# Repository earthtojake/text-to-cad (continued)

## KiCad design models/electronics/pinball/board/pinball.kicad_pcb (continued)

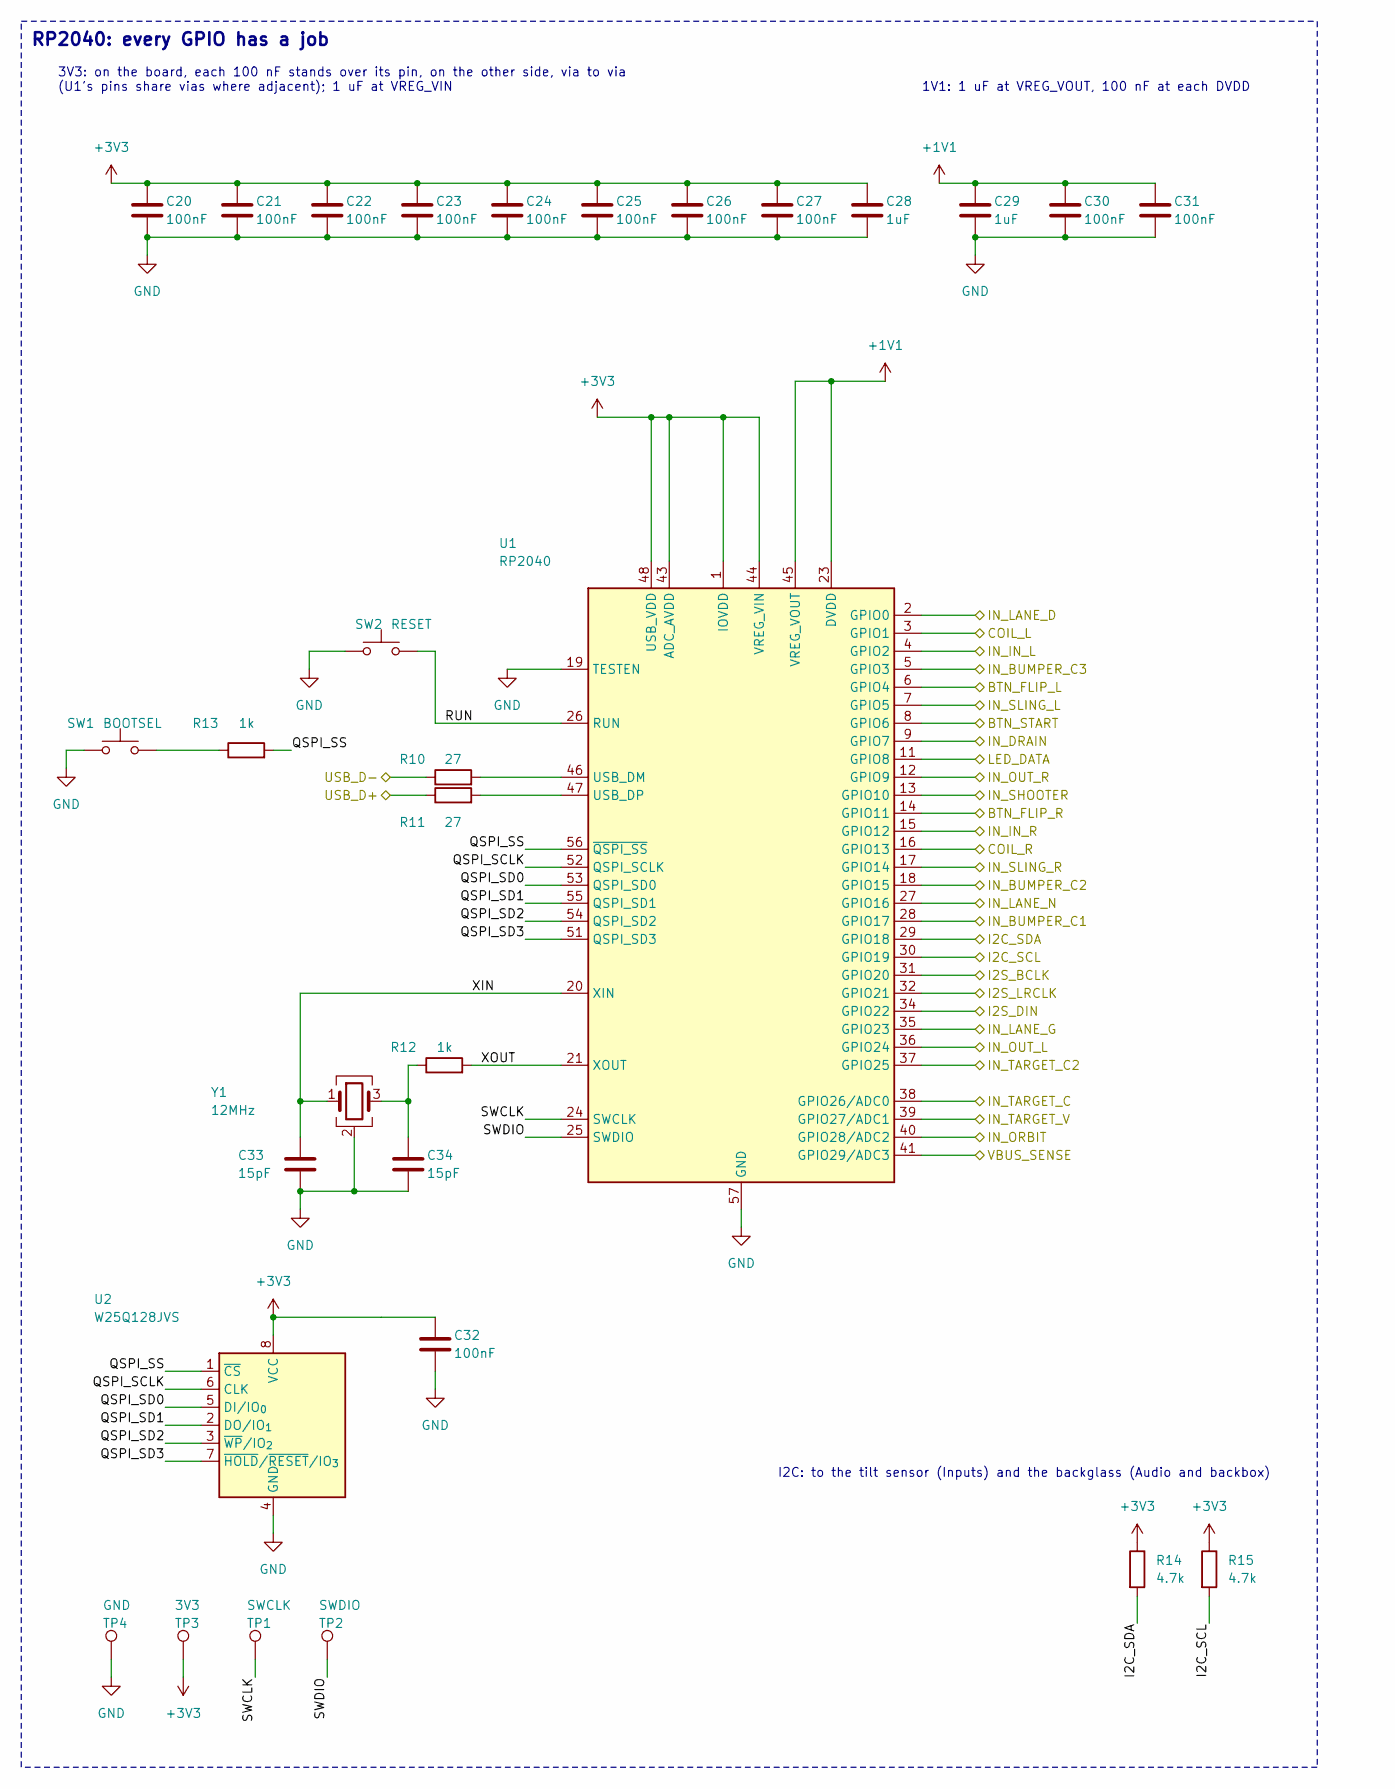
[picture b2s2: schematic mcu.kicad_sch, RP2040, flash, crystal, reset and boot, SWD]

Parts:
C20, C21, C22, C23, C24, C25, C26, C27, C30, C31, C32: 100nF; C_0402_1005Metric; MPN CL05B104KO5NNNC; LCSC C1525
C28: 1uF; C_0603_1608Metric; MPN CL10A105KB8NNNC; LCSC C15849
C29: 1uF; C_0402_1005Metric; MPN CL05A105KA5NQNC; LCSC C52923
C33, C34: 15pF; C_0402_1005Metric; MPN 0402CG150J500NT; LCSC C1548
R10, R11: 27; R_0402_1005Metric; MPN 0402WGF270JTCE; LCSC C25092
R12, R13: 1k; R_0402_1005Metric; MPN 0402WGF1001TCE; LCSC C11702
R14, R15: 4.7k; R_0402_1005Metric; MPN 0402WGF4701TCE; LCSC C25900
SW1: BOOTSEL; SW_SPST_TL3342; MPN TL3342F160QG
SW2: RESET; SW_SPST_TL3342; MPN TL3342F160QG
TP1: SWCLK; TestPoint_Pad_D1.5mm
TP2: SWDIO; TestPoint_Pad_D1.5mm
TP3: 3V3; TestPoint_Pad_D1.5mm
TP4: GND; TestPoint_Pad_D1.5mm
U1: RP2040; QFN-56-1EP_7x7mm_P0.4mm_EP3.2x3.2mm; MPN RP2040; LCSC C2040
U2: W25Q128JVS; SOIC-8_5.3x5.3mm_P1.27mm; MPN W25Q128JVSIQ; LCSC C97521
Y1: 12MHz; Crystal_SMD_3225-4Pin_3.2x2.5mm; MPN X322512MSB4SI; LCSC C9002

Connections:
+1V1: C29.1, C30.1, C31.1, U1.23 (DVDD), U1.45 (VREG_VOUT), U1.50 (DVDD)
+3V3: C20.1, C21.1, C22.1, C23.1, C24.1, C25.1, C26.1, C27.1, C28.1, C32.1, R14.1, R15.1, TP3.1 (1_1), U1.1 (IOVDD), U1.10 (IOVDD), U1.22 (IOVDD), U1.33 (IOVDD), U1.42 (IOVDD), U1.43 (ADC_AVDD), U1.44 (VREG_VIN), U1.48 (USB_VDD), U1.49 (IOVDD), U2.8 (VCC); also elsewhere on the board
/Audio and backbox/I2S_BCLK: U1.31 (GPIO20); also elsewhere on the board
/Audio and backbox/I2S_DIN: U1.34 (GPIO22); also elsewhere on the board
/Audio and backbox/I2S_LRCLK: U1.32 (GPIO21); also elsewhere on the board
/Flippers/COIL_L: U1.3 (GPIO1); also elsewhere on the board
/Flippers/COIL_R: U1.16 (GPIO13); also elsewhere on the board
/I2C_SCL: R15.2, U1.30 (GPIO19); also elsewhere on the board
/I2C_SDA: R14.2, U1.29 (GPIO18); also elsewhere on the board
/Inputs/BTN_FLIP_L: U1.6 (GPIO4); also elsewhere on the board
/Inputs/BTN_FLIP_R: U1.14 (GPIO11); also elsewhere on the board
/Inputs/BTN_START: U1.8 (GPIO6); also elsewhere on the board
/Inputs/IN_BUMPER_C1: U1.28 (GPIO17); also elsewhere on the board
/Inputs/IN_BUMPER_C2: U1.18 (GPIO15); also elsewhere on the board
/Inputs/IN_BUMPER_C3: U1.5 (GPIO3); also elsewhere on the board
/Inputs/IN_DRAIN: U1.9 (GPIO7); also elsewhere on the board
/Inputs/IN_IN_L: U1.4 (GPIO2); also elsewhere on the board
/Inputs/IN_IN_R: U1.15 (GPIO12); also elsewhere on the board
/Inputs/IN_LANE_D: U1.2 (GPIO0); also elsewhere on the board
/Inputs/IN_LANE_G: U1.35 (GPIO23); also elsewhere on the board
/Inputs/IN_LANE_N: U1.27 (GPIO16); also elsewhere on the board
/Inputs/IN_ORBIT: U1.40 (GPIO28/ADC2); also elsewhere on the board
/Inputs/IN_OUT_L: U1.36 (GPIO24); also elsewhere on the board
/Inputs/IN_OUT_R: U1.12 (GPIO9); also elsewhere on the board
/Inputs/IN_SHOOTER: U1.13 (GPIO10); also elsewhere on the board
/Inputs/IN_SLING_L: U1.7 (GPIO5); also elsewhere on the board
/Inputs/IN_SLING_R: U1.17 (GPIO14); also elsewhere on the board
/Inputs/IN_TARGET_C: U1.38 (GPIO26/ADC0); also elsewhere on the board
/Inputs/IN_TARGET_C2: U1.37 (GPIO25); also elsewhere on the board
/Inputs/IN_TARGET_V: U1.39 (GPIO27/ADC1); also elsewhere on the board
/Lighting/LED_DATA: U1.11 (GPIO8); also elsewhere on the board
/MCU/QSPI_SCLK: U1.52 (QSPI_SCLK), U2.6 (CLK)
/MCU/QSPI_SD0: U1.53 (QSPI_SD0), U2.5 (DI/IO_{0})
/MCU/QSPI_SD1: U1.55 (QSPI_SD1), U2.2 (DO/IO_{1})
/MCU/QSPI_SD2: U1.54 (QSPI_SD2), U2.3 (~WP/IO_{2})
/MCU/QSPI_SD3: U1.51 (QSPI_SD3), U2.7 (~HOLD/~RESET/IO_{3})
/MCU/QSPI_SS: R13.2, U1.56 (~QSPI_SS), U2.1 (~CS)
/MCU/RUN: SW2.2, U1.26 (RUN)
/MCU/SWCLK: TP1.1 (1_1), U1.24 (SWCLK)
/MCU/SWDIO: TP2.1 (1_1), U1.25 (SWDIO)
/MCU/VBUS_SENSE: U1.41 (GPIO29/ADC3); also elsewhere on the board
/MCU/XIN: C33.1, U1.20 (XIN), Y1.1
/MCU/XOUT: R12.2, U1.21 (XOUT)
/Power/USB_D+: R11.1; also elsewhere on the board
/Power/USB_D-: R10.1; also elsewhere on the board
GND: C20.2, C21.2, C22.2, C23.2, C24.2, C25.2, C26.2, C27.2, C28.2, C29.2, C30.2, C31.2, C32.2, C33.2, C34.2, SW1.1, SW2.1, TP4.1 (1_1), U1.19 (TESTEN), U1.57 (GND), U2.4 (GND), Y1.2 (G), Y1.4 (G); also elsewhere on the board
unnamed: C34.1, R12.1, Y1.3
unnamed: R13.1, SW1.2
unnamed: R10.2, U1.46 (USB_DM)
unnamed: R11.2, U1.47 (USB_DP)

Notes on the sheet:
RP2040: every GPIO has a job
3V3: on the board, each 100 nF stands over its pin, on the other side, via to via (U1's pins share vias where adjacent); 1 uF at VREG_VIN
1V1: 1 uF at VREG_VOUT, 100 nF at each DVDD
I2C: to the tilt sensor (Inputs) and the backglass (Audio and backbox)

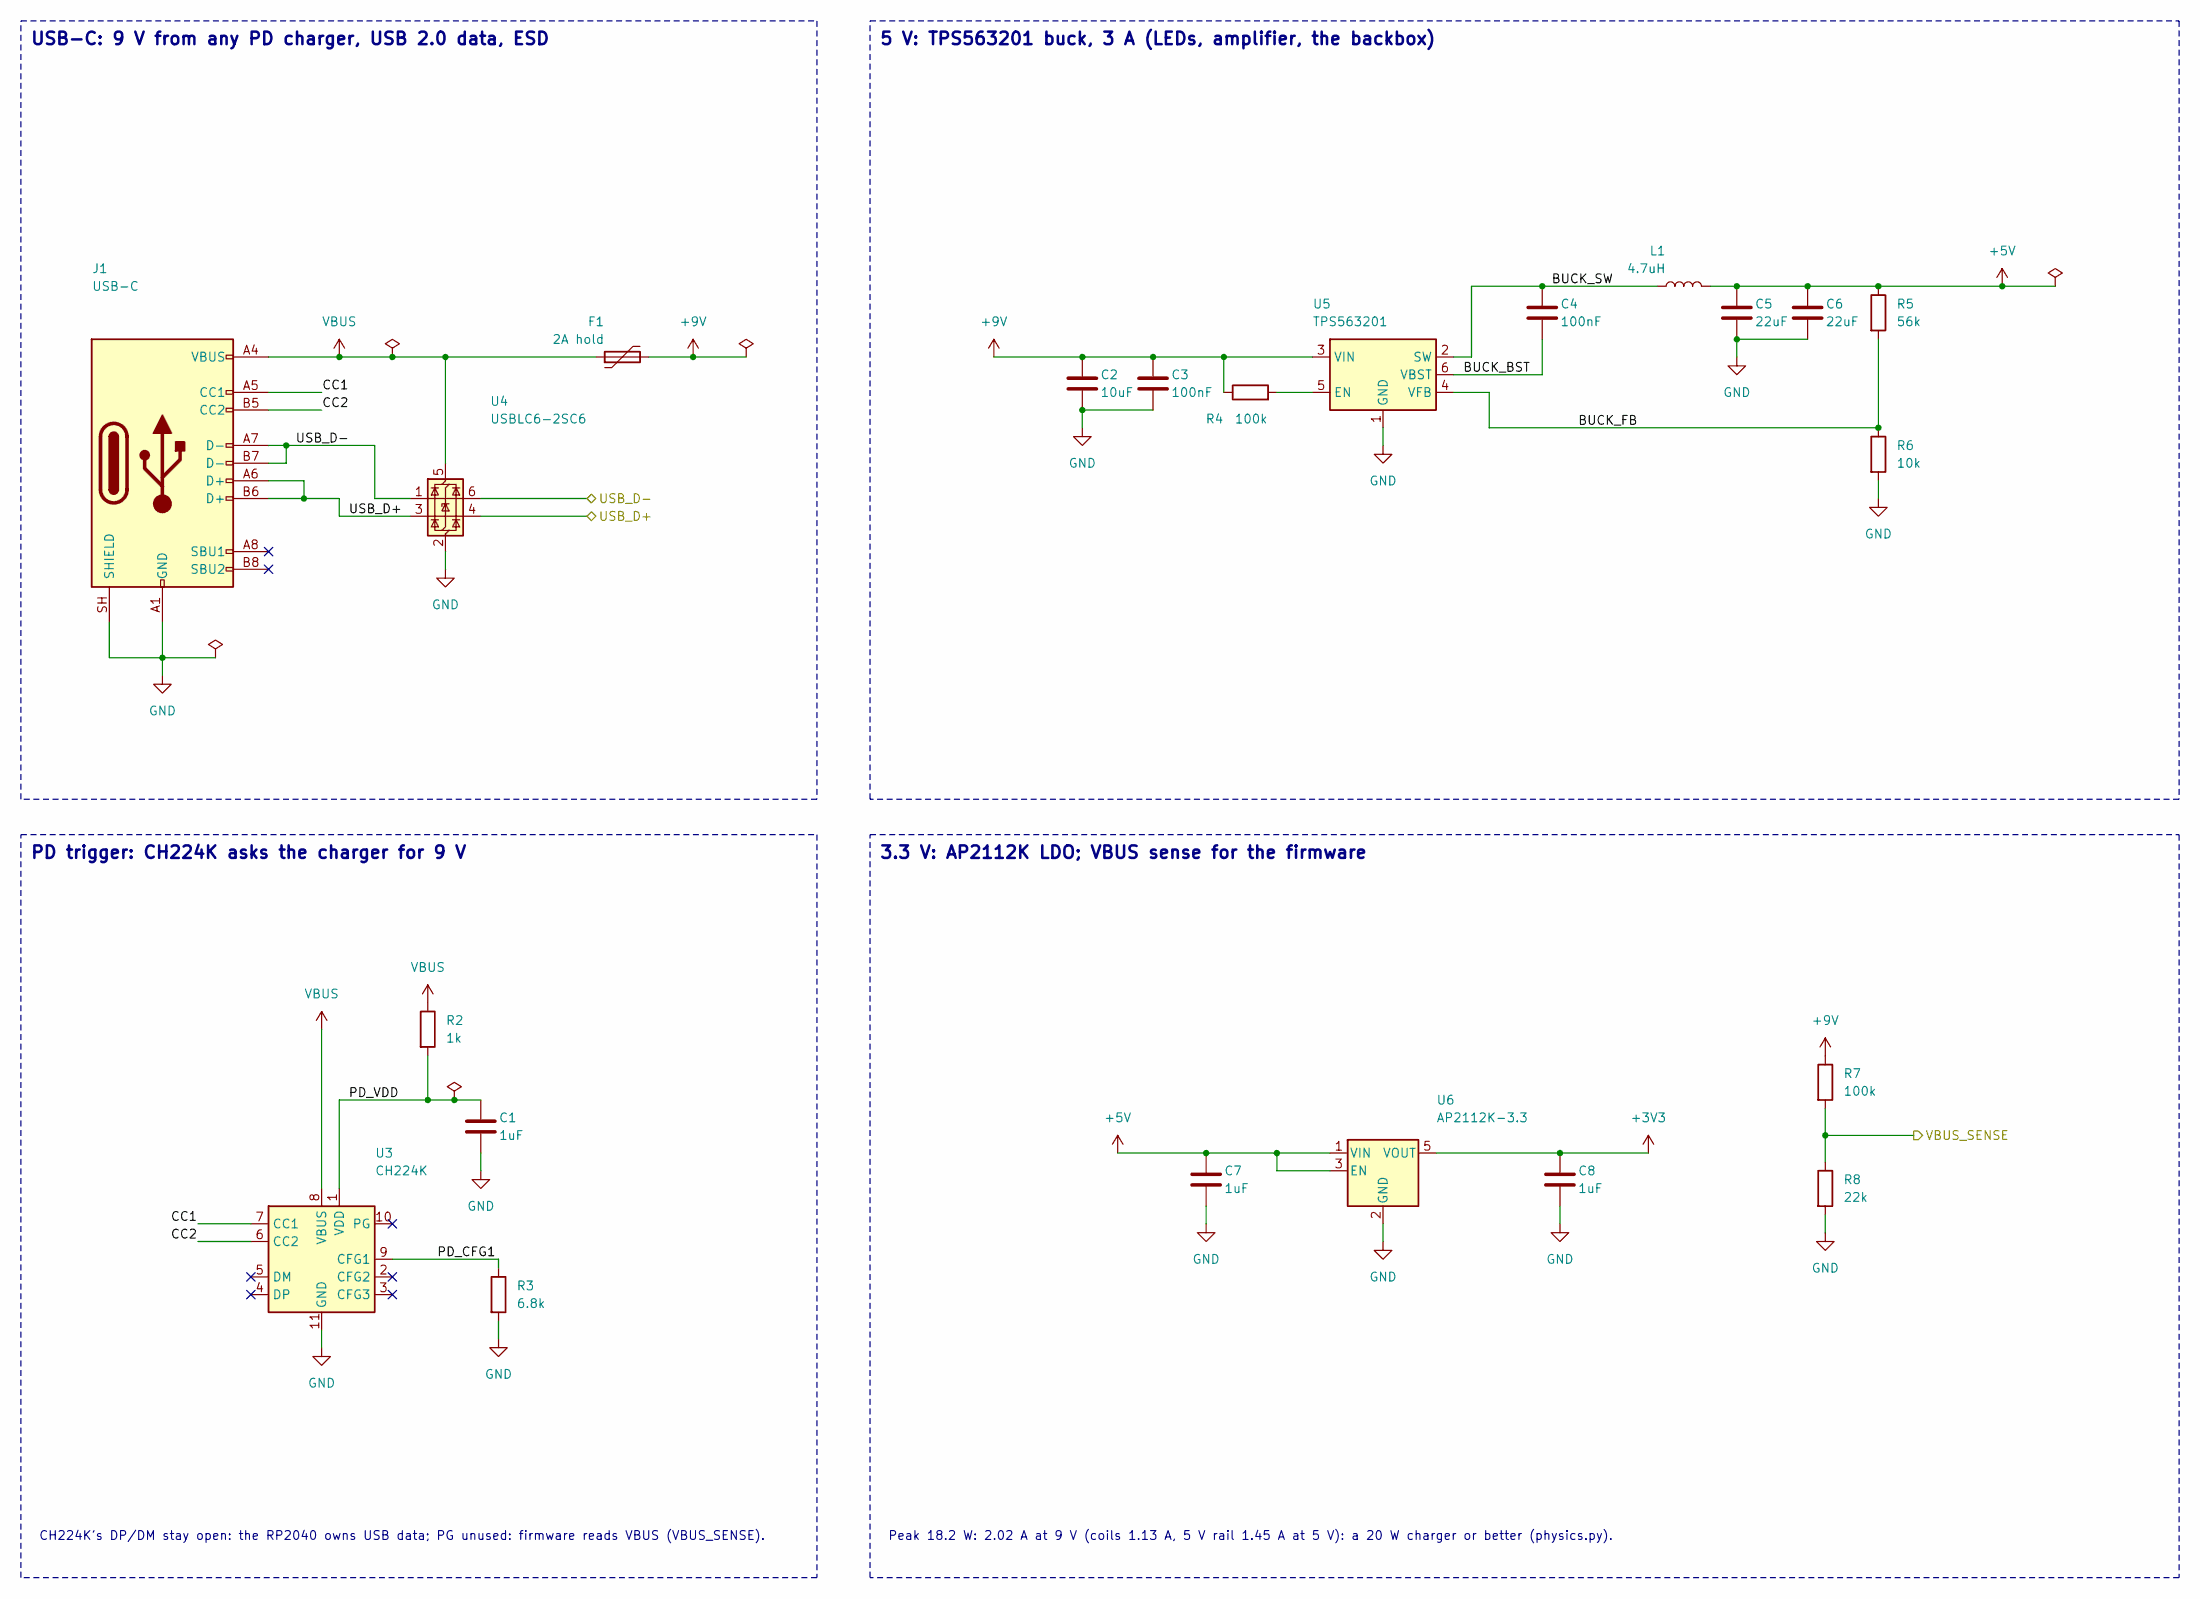
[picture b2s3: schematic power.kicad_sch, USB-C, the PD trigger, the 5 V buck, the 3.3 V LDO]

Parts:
C1, C7, C8: 1uF; C_0603_1608Metric; MPN CL10A105KB8NNNC; LCSC C15849
C2: 10uF; C_0805_2012Metric; MPN CL21A106KAYNNNE; LCSC C15850
C3, C4: 100nF; C_0402_1005Metric; MPN CL05B104KO5NNNC; LCSC C1525
C5, C6: 22uF; C_0805_2012Metric; MPN CL21A226MAQNNNE; LCSC C45783
F1: 2A hold; Fuse_1210_3225Metric; MPN 1210L200SLYR
J1: USB-C; USB_C_Receptacle_HRO_TYPE-C-31-M-12; MPN TYPE-C-31-M-12; LCSC C165948
L1: 4.7uH; L_Changjiang_FNR4020S; MPN FNR4020S4R7MT; LCSC C167219
R2: 1k; R_0402_1005Metric; MPN 0402WGF1001TCE; LCSC C11702
R3: 6.8k; R_0402_1005Metric; MPN 0402WGF6801TCE; LCSC C25917
R4, R7: 100k; R_0402_1005Metric; MPN 0402WGF1003TCE; LCSC C25741
R5: 56k; R_0402_1005Metric; MPN 0402WGF5602TCE; LCSC C25796
R6: 10k; R_0402_1005Metric; MPN 0402WGF1002TCE; LCSC C25744
R8: 22k; R_0402_1005Metric; MPN 0402WGF2202TCE; LCSC C25768
U3: CH224K; SSOP-10-1EP_3.9x4.9mm_P1mm_EP2.1x3.3mm; MPN CH224K; LCSC C970725
U4: USBLC6-2SC6; SOT-23-6; MPN USBLC6-2SC6; LCSC C7519
U5: TPS563201; SOT-23-6; MPN TPS563201DDCR; LCSC C116592
U6: AP2112K-3.3; SOT-23-5; MPN AP2112K-3.3TRG1; LCSC C51118

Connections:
+3V3: C8.1, U6.5 (VOUT); also elsewhere on the board
+5V: C5.1, C6.1, C7.1, L1.2, R5.1, U6.1 (VIN), U6.3 (EN); also elsewhere on the board
+9V: C2.1, C3.1, F1.2, R4.1, R7.1, U5.3 (VIN); also elsewhere on the board
/MCU/VBUS_SENSE: R7.2, R8.1; also elsewhere on the board
/Power/BUCK_BST: C4.1, U5.6 (VBST)
/Power/BUCK_FB: R5.2, R6.1, U5.4 (VFB)
/Power/BUCK_SW: C4.2, L1.1, U5.2 (SW)
/Power/CC1: J1.A5 (CC1), U3.7 (CC1)
/Power/CC2: J1.B5 (CC2), U3.6 (CC2)
/Power/PD_CFG1: R3.1, U3.9 (CFG1)
/Power/PD_VDD: C1.1, R2.2, U3.1 (VDD)
/Power/USB_D+: J1.A6 (D+), J1.B6 (D+), U4.3 (I/O2), U4.4 (I/O2); also elsewhere on the board
/Power/USB_D-: J1.A7 (D-), J1.B7 (D-), U4.1 (I/O1), U4.6 (I/O1); also elsewhere on the board
GND: C1.2, C2.2, C3.2, C5.2, C6.2, C7.2, C8.2, J1.A1 (GND), J1.A12 (GND), J1.B1 (GND), J1.B12 (GND), J1.SH (SHIELD), R3.2, R6.2, R8.2, U3.11 (GND), U4.2 (GND), U5.1 (GND), U6.2 (GND); also elsewhere on the board
unnamed: R4.2, U5.5 (EN)
VBUS: F1.1, J1.A4 (VBUS), J1.A9 (VBUS), J1.B4 (VBUS), J1.B9 (VBUS), R2.1, U3.8 (VBUS), U4.5 (VBUS)

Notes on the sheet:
USB-C: 9 V from any PD charger, USB 2.0 data, ESD
PD trigger: CH224K asks the charger for 9 V
CH224K's DP/DM stay open: the RP2040 owns USB data; PG unused: firmware reads VBUS (VBUS_SENSE).
5 V: TPS563201 buck, 3 A (LEDs, amplifier, the backbox)
3.3 V: AP2112K LDO; VBUS sense for the firmware
Peak 18.2 W: 2.02 A at 9 V (coils 1.13 A, 5 V rail 1.45 A at 5 V): a 20 W charger or better (physics.py).

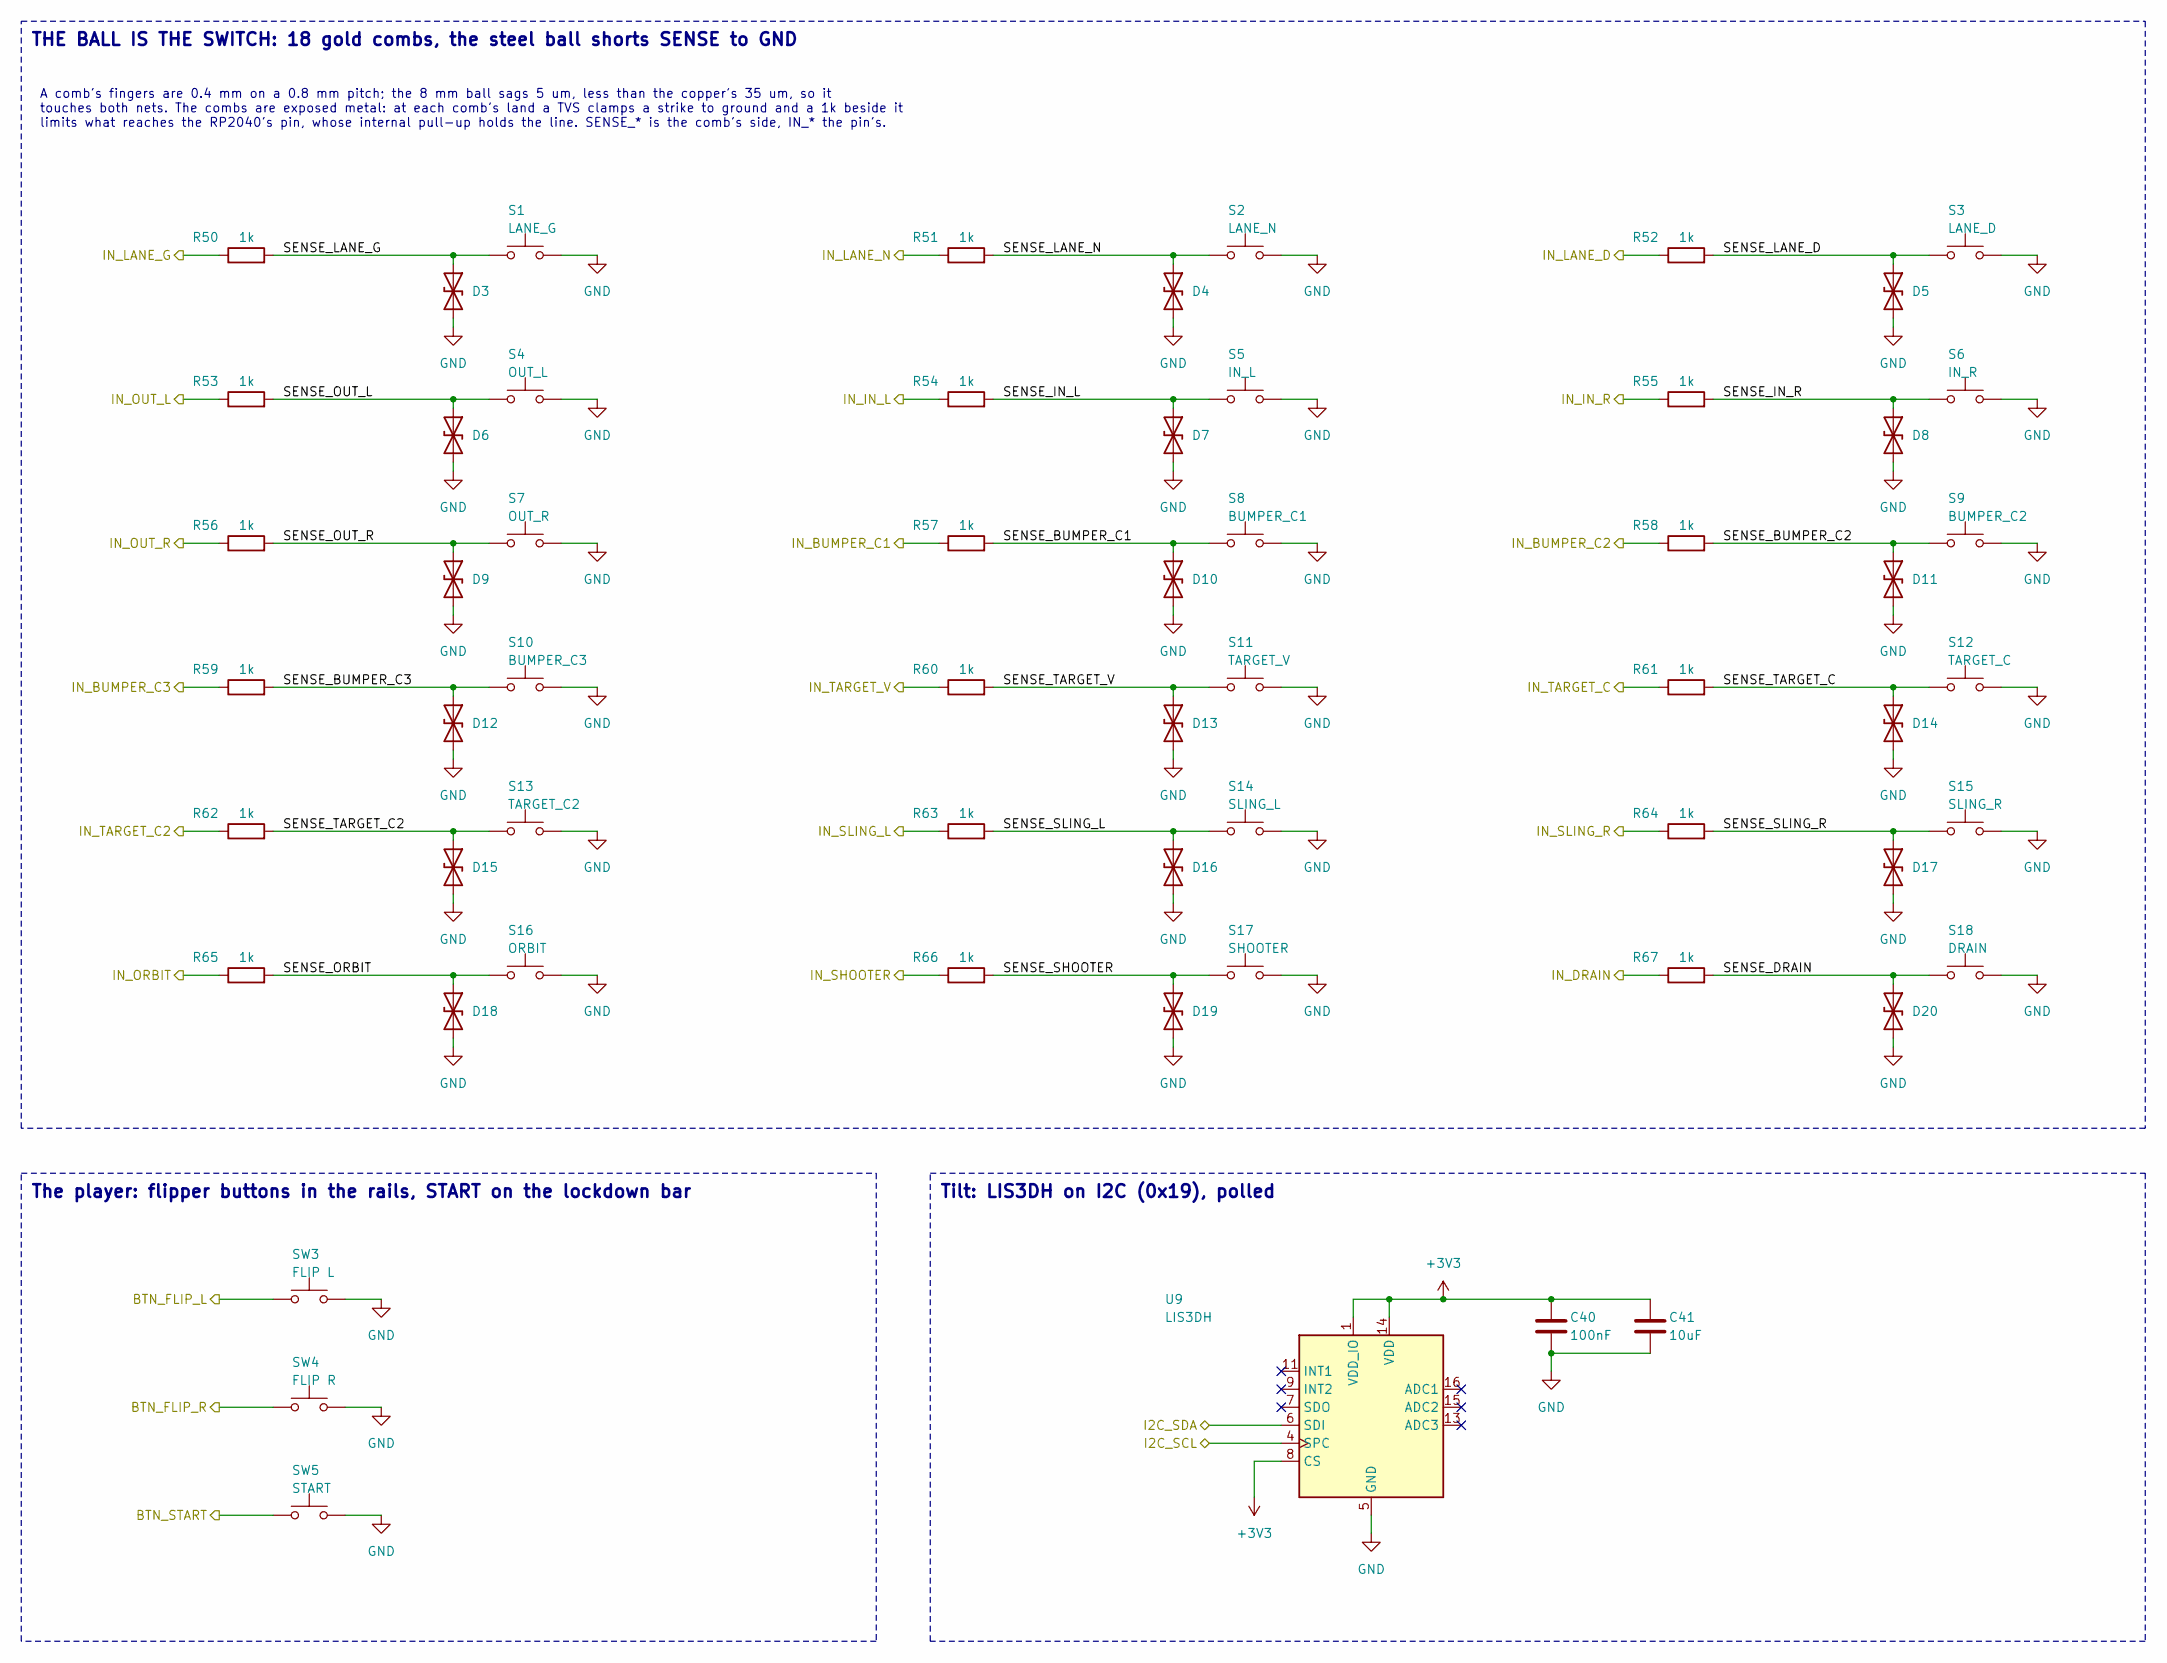
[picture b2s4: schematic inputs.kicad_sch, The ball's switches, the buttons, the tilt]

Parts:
C40: 100nF; C_0402_1005Metric; MPN CL05B104KO5NNNC; LCSC C1525
C41: 10uF; C_0805_2012Metric; MPN CL21A106KAYNNNE; LCSC C15850
D3, D4, D5, D6, D7, D8, D9, D10, D11, D12, D13, D14, D15, D16, D17, D18, D19, D20: PESD5V0S1BA; D_SOD-323; MPN PESD5V0S1BA,115
R50, R51, R52, R53, R54, R55, R56, R57, R58, R59, R60, R61, R62, R63, R64, R65, R66, R67: 1k; R_0402_1005Metric; MPN 0402WGF1001TCE; LCSC C11702
S1: LANE_G; Comb_S1
S2: LANE_N; Comb_S2
S3: LANE_D; Comb_S3
S4: OUT_L; Comb_S4
S5: IN_L; Comb_S5
S6: IN_R; Comb_S6
S7: OUT_R; Comb_S7
S8: BUMPER_C1; Comb_S8
S9: BUMPER_C2; Comb_S9
S10: BUMPER_C3; Comb_S10
S11: TARGET_V; Comb_S11
S12: TARGET_C; Comb_S12
S13: TARGET_C2; Comb_S13
S14: SLING_L; Comb_S14
S15: SLING_R; Comb_S15
S16: ORBIT; Comb_S16
S17: SHOOTER; Comb_S17
S18: DRAIN; Comb_S18
SW3: FLIP L; SW_Tactile_SPST_Angled_PTS645Vx58-2LFS; MPN PTS645VL58-2 LFS
SW4: FLIP R; SW_Tactile_SPST_Angled_PTS645Vx58-2LFS; MPN PTS645VL58-2 LFS
SW5: START; SW_PUSH_6mm_H9.5mm
U9: LIS3DH; LGA-16_3x3mm_P0.5mm_LayoutBorder3x5y; MPN LIS3DHTR; LCSC C15134

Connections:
+3V3: C40.1, C41.1, U9.1 (VDD_IO), U9.8 (CS), U9.14 (VDD); also elsewhere on the board
/I2C_SCL: U9.4 (SPC); also elsewhere on the board
/I2C_SDA: U9.6 (SDI); also elsewhere on the board
/Inputs/BTN_FLIP_L: SW3.1; also elsewhere on the board
/Inputs/BTN_FLIP_R: SW4.1; also elsewhere on the board
/Inputs/BTN_START: SW5.1; also elsewhere on the board
/Inputs/IN_BUMPER_C1: R57.1; also elsewhere on the board
/Inputs/IN_BUMPER_C2: R58.1; also elsewhere on the board
/Inputs/IN_BUMPER_C3: R59.1; also elsewhere on the board
/Inputs/IN_DRAIN: R67.1; also elsewhere on the board
/Inputs/IN_IN_L: R54.1; also elsewhere on the board
/Inputs/IN_IN_R: R55.1; also elsewhere on the board
/Inputs/IN_LANE_D: R52.1; also elsewhere on the board
/Inputs/IN_LANE_G: R50.1; also elsewhere on the board
/Inputs/IN_LANE_N: R51.1; also elsewhere on the board
/Inputs/IN_ORBIT: R65.1; also elsewhere on the board
/Inputs/IN_OUT_L: R53.1; also elsewhere on the board
/Inputs/IN_OUT_R: R56.1; also elsewhere on the board
/Inputs/IN_SHOOTER: R66.1; also elsewhere on the board
/Inputs/IN_SLING_L: R63.1; also elsewhere on the board
/Inputs/IN_SLING_R: R64.1; also elsewhere on the board
/Inputs/IN_TARGET_C: R61.1; also elsewhere on the board
/Inputs/IN_TARGET_C2: R62.1; also elsewhere on the board
/Inputs/IN_TARGET_V: R60.1; also elsewhere on the board
/Inputs/SENSE_BUMPER_C1: D10.1 (A1), R57.2, S8.1
/Inputs/SENSE_BUMPER_C2: D11.1 (A1), R58.2, S9.1
/Inputs/SENSE_BUMPER_C3: D12.1 (A1), R59.2, S10.1
/Inputs/SENSE_DRAIN: D20.1 (A1), R67.2, S18.1
/Inputs/SENSE_IN_L: D7.1 (A1), R54.2, S5.1
/Inputs/SENSE_IN_R: D8.1 (A1), R55.2, S6.1
/Inputs/SENSE_LANE_D: D5.1 (A1), R52.2, S3.1
/Inputs/SENSE_LANE_G: D3.1 (A1), R50.2, S1.1
/Inputs/SENSE_LANE_N: D4.1 (A1), R51.2, S2.1
/Inputs/SENSE_ORBIT: D18.1 (A1), R65.2, S16.1
/Inputs/SENSE_OUT_L: D6.1 (A1), R53.2, S4.1
/Inputs/SENSE_OUT_R: D9.1 (A1), R56.2, S7.1
/Inputs/SENSE_SHOOTER: D19.1 (A1), R66.2, S17.1
/Inputs/SENSE_SLING_L: D16.1 (A1), R63.2, S14.1
/Inputs/SENSE_SLING_R: D17.1 (A1), R64.2, S15.1
/Inputs/SENSE_TARGET_C: D14.1 (A1), R61.2, S12.1
/Inputs/SENSE_TARGET_C2: D15.1 (A1), R62.2, S13.1
/Inputs/SENSE_TARGET_V: D13.1 (A1), R60.2, S11.1
GND: C40.2, C41.2, D3.2 (A2), D4.2 (A2), D5.2 (A2), D6.2 (A2), D7.2 (A2), D8.2 (A2), D9.2 (A2), D10.2 (A2), D11.2 (A2), D12.2 (A2), D13.2 (A2), D14.2 (A2), D15.2 (A2), D16.2 (A2), D17.2 (A2), D18.2 (A2), D19.2 (A2), D20.2 (A2), S1.2, S2.2, S3.2, S4.2, S5.2, S6.2, S7.2, S8.2, S9.2, S10.2, S11.2, S12.2, S13.2, S14.2, S15.2, S16.2, S17.2, S18.2, SW3.2, SW4.2, SW5.2, U9.5 (GND), U9.10 (GND), U9.12 (GND); also elsewhere on the board

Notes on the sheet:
THE BALL IS THE SWITCH: 18 gold combs, the steel ball shorts SENSE to GND
A comb's fingers are 0.4 mm on a 0.8 mm pitch; the 8 mm ball sags 5 um, less than the copper's 35 um, so it touches both nets. The combs are exposed metal: at each comb's land a TVS clamps a strike to ground and a 1k beside it limits what reaches the RP2040's pin, whose internal pull-up holds the l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
The player: flipper buttons in the rails, START on the lockdown bar
Tilt: LIS3DH on I2C (0x19), polled
